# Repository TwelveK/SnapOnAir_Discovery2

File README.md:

# SnapOnAir_Discovery2
LORA communicator 2018 Version

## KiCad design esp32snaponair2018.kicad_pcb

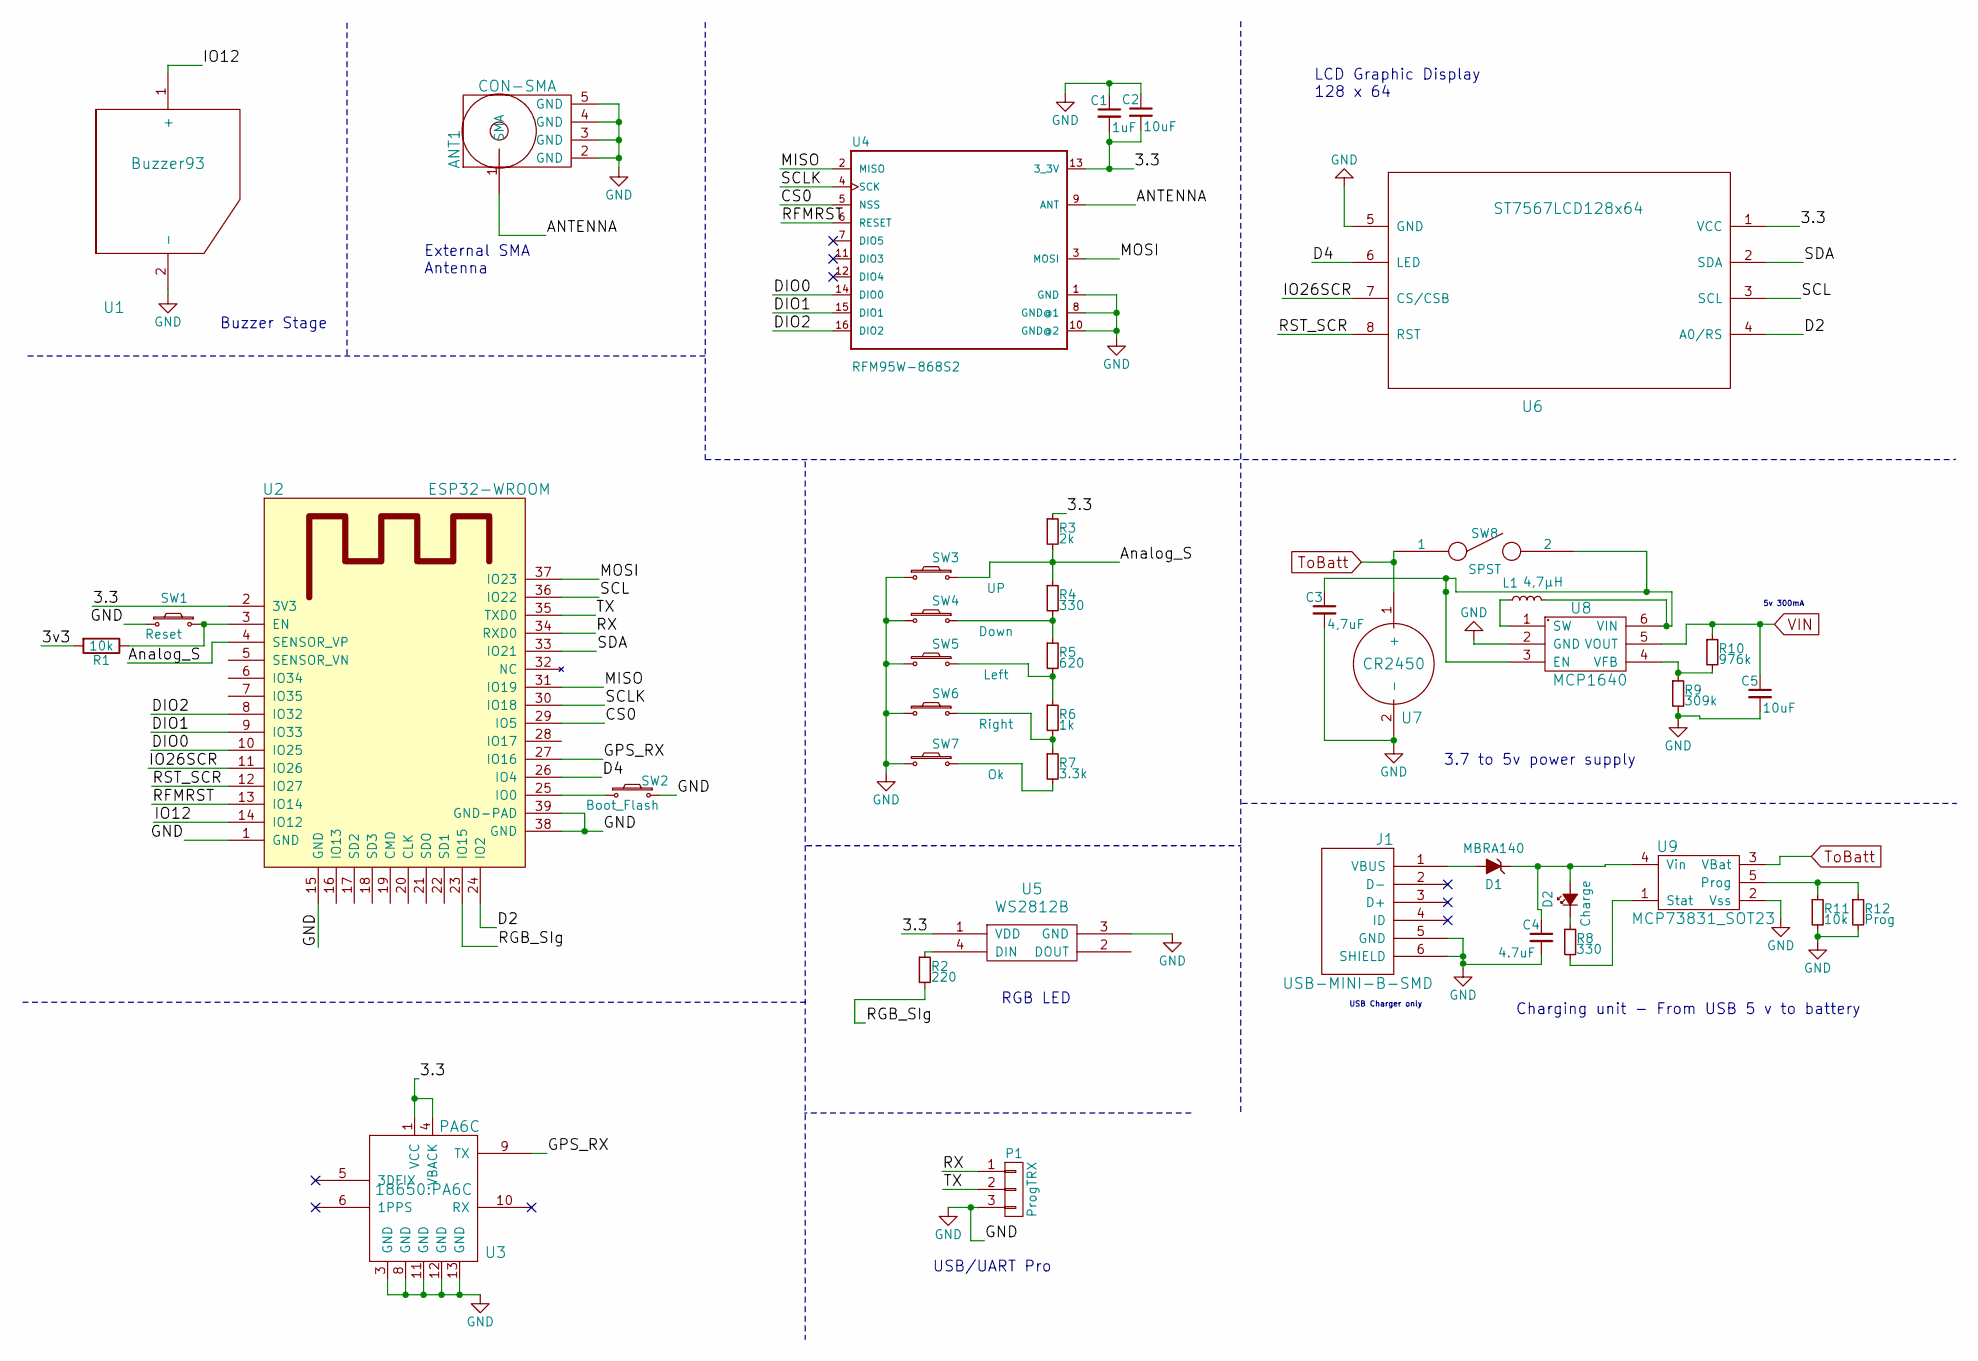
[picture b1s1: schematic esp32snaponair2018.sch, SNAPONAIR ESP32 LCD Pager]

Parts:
ANT1: CON-SMA; SMA_EDGE
C1: 1uF; C_1206_HandSoldering
C2, C5: 10uF; C_1206_HandSoldering
C3: 4,7uF; C_1206_HandSoldering
C4: 4.7uF; C_1206_HandSoldering
D1: MBRA140; MBRA140-Zenner
D2: Charge; LED_1206_HandSoldering
J1: USB-MINI-B-SMD; USB_Micro-B
L1: 4,7µH; Choke_CD54
P1: ProgTRX; Socket_Strip_Straight_1x03_Pitch2.54mm
R1: 10k
R2: 220; R_1206_HandSoldering
R3: 2k; R_1206_HandSoldering
R4, R8: 330; R_1206_HandSoldering
R5: 620; R_1206_HandSoldering
R6: 1k; R_1206_HandSoldering
R7: 3.3k; R_1206_HandSoldering
R9: 309k; R_1206_HandSoldering
R10: 976k; R_1206_HandSoldering
R11: 10k; R_1206_HandSoldering
R12: Prog; R_1206_HandSoldering
SW1: Reset; SW_SPST_B3U-1000P
SW2: Boot_Flash; SW_SPST_B3U-1000P
SW3: UP; SW_SPST_B3S-1000
SW4: Down; SW_SPST_B3S-1000
SW5: Left; SW_SPST_B3S-1000
SW6: Right; SW_SPST_B3S-1000
SW7: Ok; SW_SPST_B3S-1000
SW8: SPST; SW_SPDT_PCM12
U1: Buzzer93
U2: ESP32-WROOM
U3: PA6C
U4: RFM95W-868S2; RFM95W
U5: WS2812B
U6: ST7567LCD128x64; LCD128x64_ST7567
U7: CR2450; BATT_CR2450_Holder
U8: MCP1640; MCP1640_SOT23-6
U9: MCP73831_SOT23; SOT-23-5_HandSoldering

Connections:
/3.3: C1.2, C2.2, R3.1, U2.2 (3V3), U3.1 (VCC), U3.4 (VBACK), U4.13 (3_3V), U5.1 (VDD), U6.1 (VCC)
/ANTENNA: ANT1.1 (SMA), U4.9 (ANT)
/Analog_S: R3.2, R4.1, SW3.2, U2.4 (SENSOR_VP)
/CS0: U2.29 (IO5), U4.5 (NSS)
/D2: U2.24 (IO2), U6.4 (A0/RS)
/D4: U2.26 (IO4), U6.6 (LED)
/DIO0: U2.10 (IO25), U4.14 (DIO0)
/DIO1: U2.9 (IO33), U4.15 (DIO1)
/DIO2: U2.8 (IO32), U4.16 (DIO2)
/GPS_RX: U2.27 (IO16), U3.9 (TX)
/IO12: U1.1 (+), U2.14 (IO12)
/IO26SCR: U2.11 (IO26), U6.7 (CS/CSB)
/MISO: U2.31 (IO19), U4.2 (MISO)
/MOSI: U2.37 (IO23), U4.3 (MOSI)
/RFMRST: U2.13 (IO14), U4.6 (RESET)
/RGB_SIg: R2.2, U2.23 (IO15)
/RST_SCR: U2.12 (IO27), U6.8 (RST)
/RX: P1.1, U2.34 (RXD0)
/SCL: U2.36 (IO22), U6.3 (SCL)
/SCLK: U2.30 (IO18), U4.4 (SCK)
/SDA: U2.33 (IO21), U6.2 (SDA)
/TX: P1.2, U2.35 (TXD0)
GND: ANT1.2 (GND), ANT1.3 (GND), ANT1.4 (GND), ANT1.5 (GND), C1.1, C2.1, C3.2, C4.2, C5.2, J1.5 (GND), J1.6 (SHIELD), P1.3, R9.2, R11.2, R12.2, SW1.1, SW2.2, SW3.1, SW4.1, SW5.1, SW6.1, SW7.1, U1.2 (-), U2.1 (GND), U2.15 (GND), U2.38 (GND), U2.39 (GND-PAD), U3.3 (GND), U3.8 (GND), U3.11 (GND), U3.12 (GND), U3.13 (GND), U4.1 (GND), U4.8 (GND@1), U4.10 (GND@2), U5.3 (GND), U6.5 (GND), U7.2 (-), U8.2 (GND), U9.2 (Vss)
unnamed: C3.1, L1.2, SW8.2, U8.3 (EN), U8.6 (VIN)
unnamed: C4.1, D1.1 (K), D2.2 (A), U9.4 (Vin)
unnamed: D1.2 (A), J1.1 (VBUS)
unnamed: D2.1 (K), R8.1
unnamed: L1.1, U8.1 (SW)
unnamed: R1.1, SW1.2, U2.3 (EN)
unnamed: R2.1, U5.4 (DIN)
unnamed: R4.2, R5.1, SW4.2
unnamed: R5.2, R6.1, SW5.2
unnamed: R6.2, R7.1, SW6.2
unnamed: R7.2, SW7.2
unnamed: R8.2, U9.1 (Stat)
unnamed: R9.1, R10.2, U8.4 (VFB)
unnamed: R11.1, R12.1, U9.5 (Prog)
unnamed: SW2.1, U2.25 (IO0)
ToBatt: SW8.1, U7.1 (+), U9.3 (VBat)
VIN: C5.1, R10.1, U8.5 (VOUT)

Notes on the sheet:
USB/UART Pro
LCD Graphic Display 128 x 64
External SMA Antenna
RGB LED
5v 300mA
USB Charger only
3.7 to 5v power supply
Charging unit - From USB 5 v to battery
Buzzer Stage

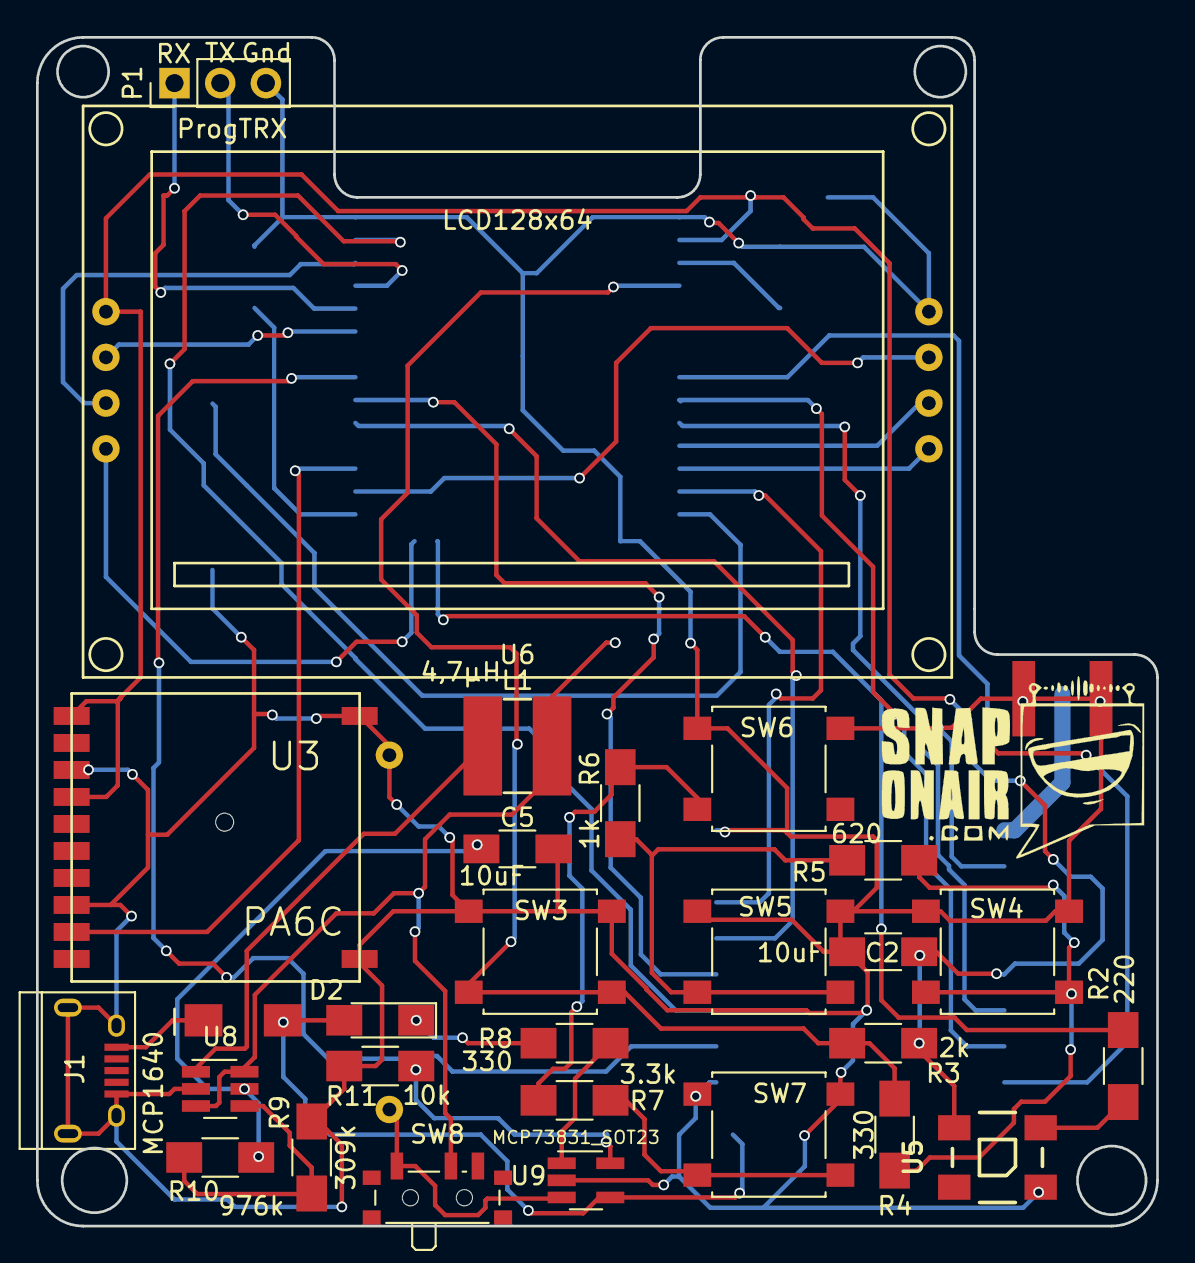
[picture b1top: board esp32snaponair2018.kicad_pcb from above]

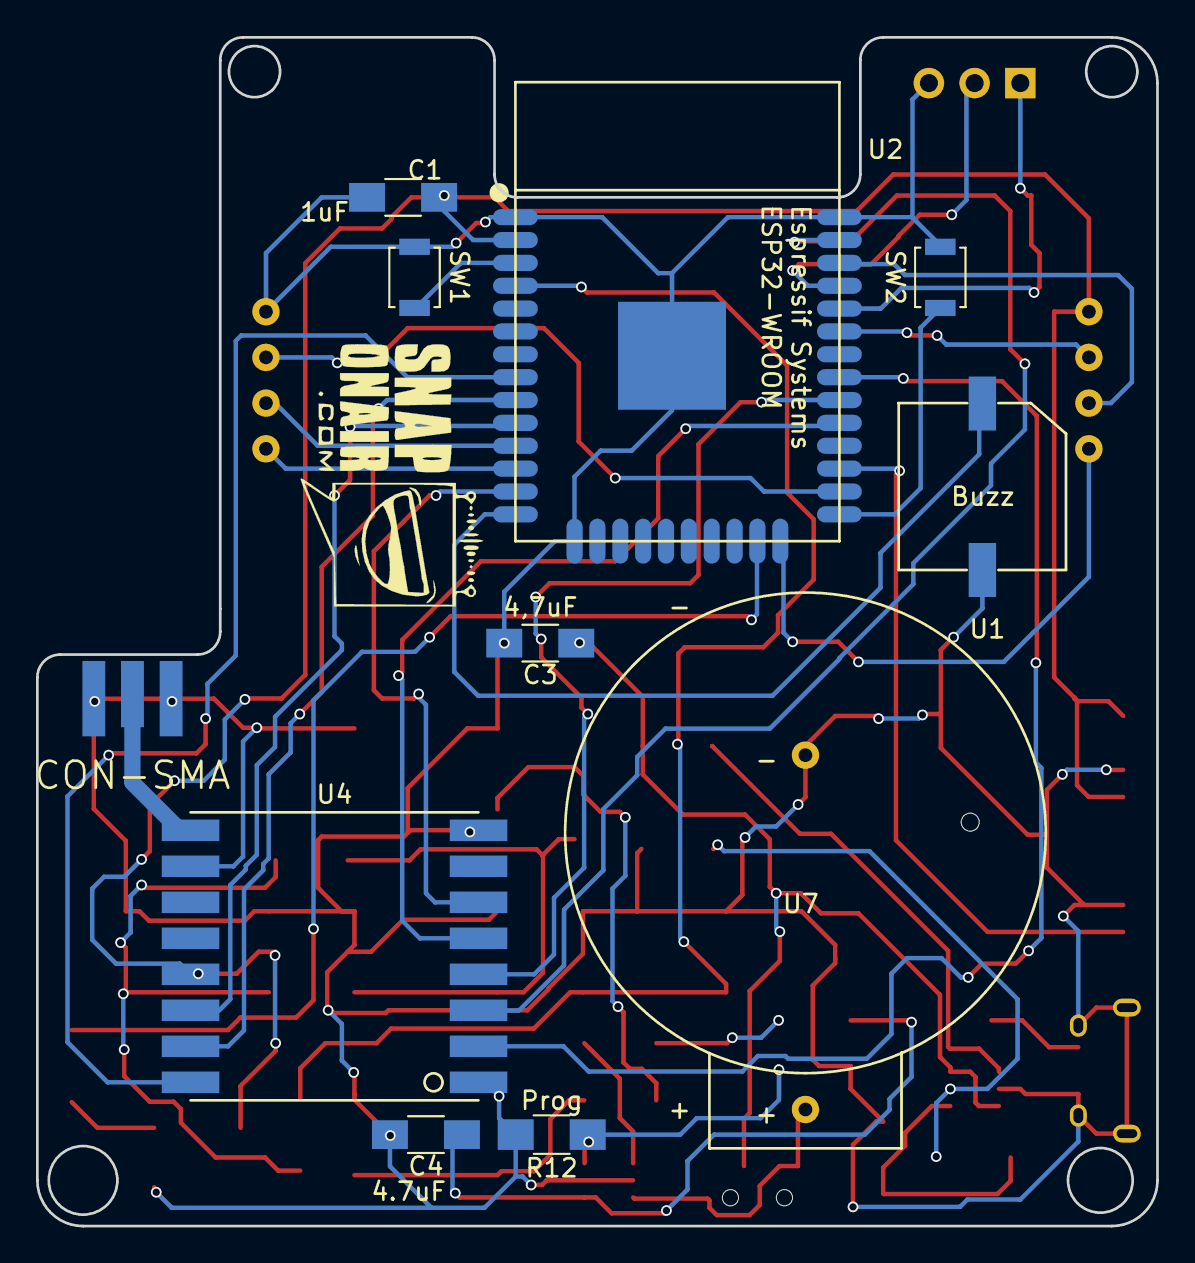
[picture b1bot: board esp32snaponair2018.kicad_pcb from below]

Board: 2 copper layers, 62.2 x 66.0 mm, 39 parts (11 on the bottom side), 40 nets.
